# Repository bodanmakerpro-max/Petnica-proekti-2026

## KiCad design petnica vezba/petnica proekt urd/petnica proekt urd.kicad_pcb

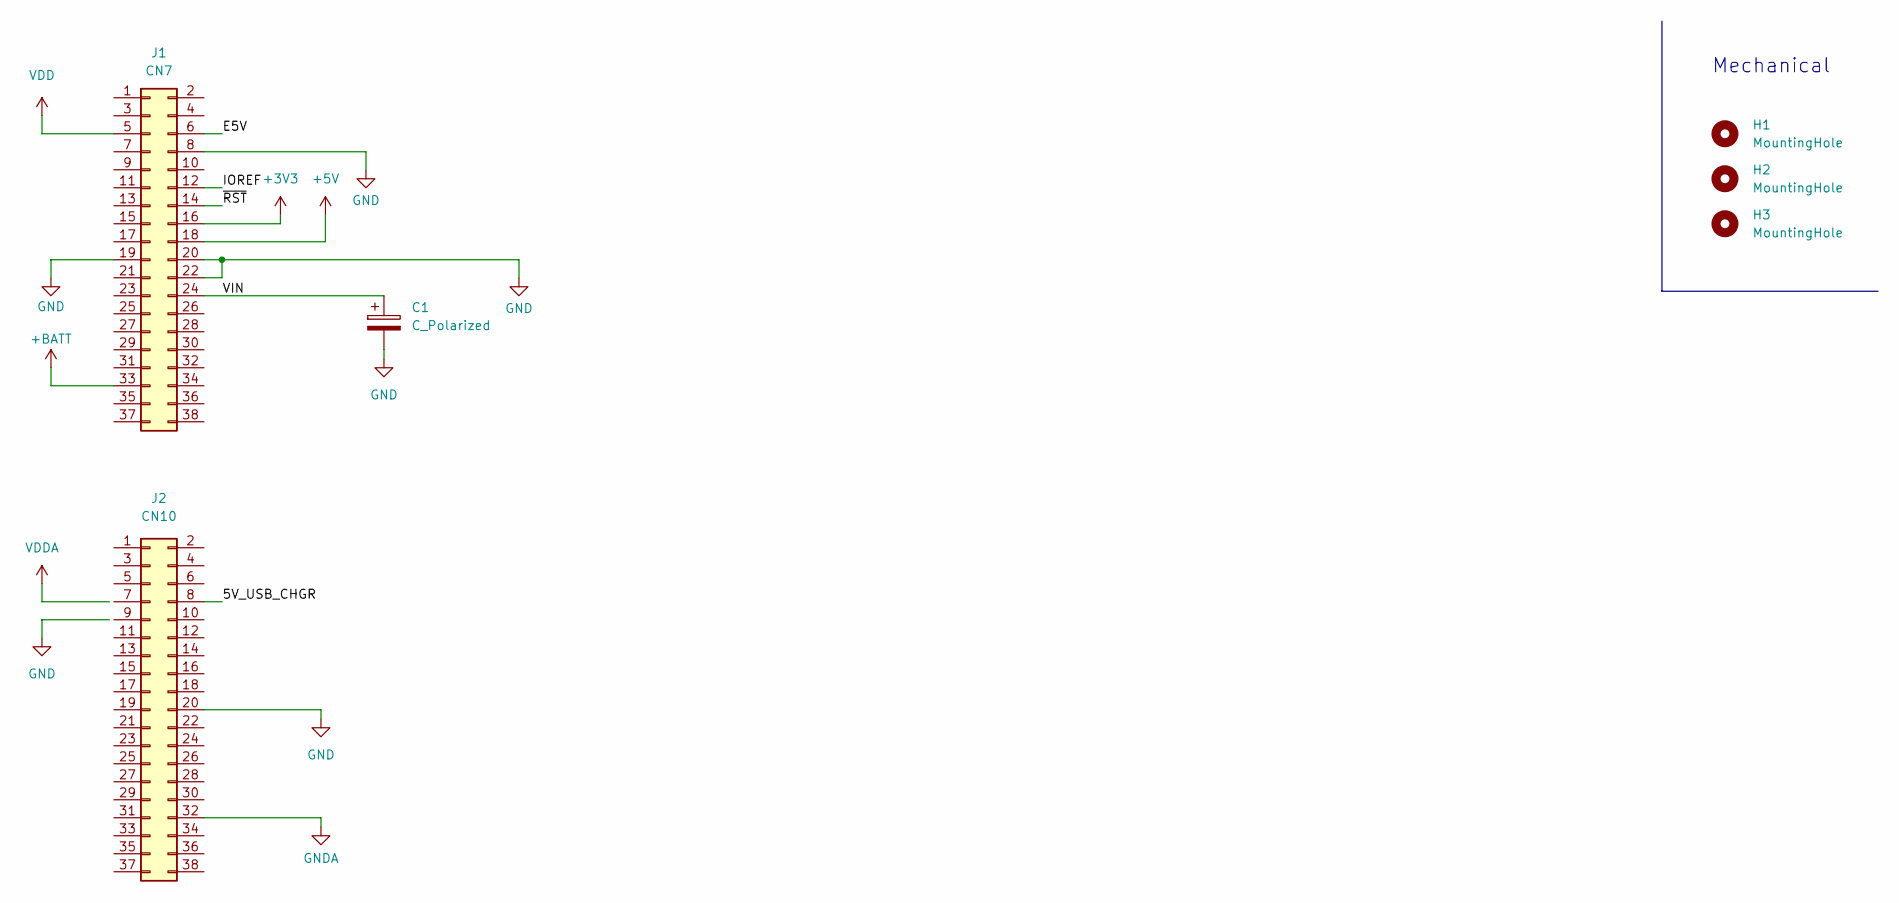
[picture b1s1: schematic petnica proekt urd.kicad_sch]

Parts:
C1: C_Polarized; CP_Radial_D13.0mm_P7.50mm
H1, H2, H3: MountingHole; MountingHole_3.2mm_M3
J1: CN7; PinSocket_2x19_P2.54mm_Vertical
J2: CN10; PinSocket_2x19_P2.54mm_Vertical

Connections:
+3V3: J1.16
+5V: J1.18
+BATT: J1.33
/5V_USB_CHGR: J2.8
/E5V: J1.6
/IOREF: J1.12
/VIN: C1.1, J1.24
/~RST: J1.14
GND: C1.2, J1.8, J1.19, J1.20, J1.22, J2.20
GNDA: J2.32
VDD: J1.5

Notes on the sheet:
Mechanical

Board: 2 copper layers, 6 parts (2 on the bottom side), 2 nets, no tracks yet.

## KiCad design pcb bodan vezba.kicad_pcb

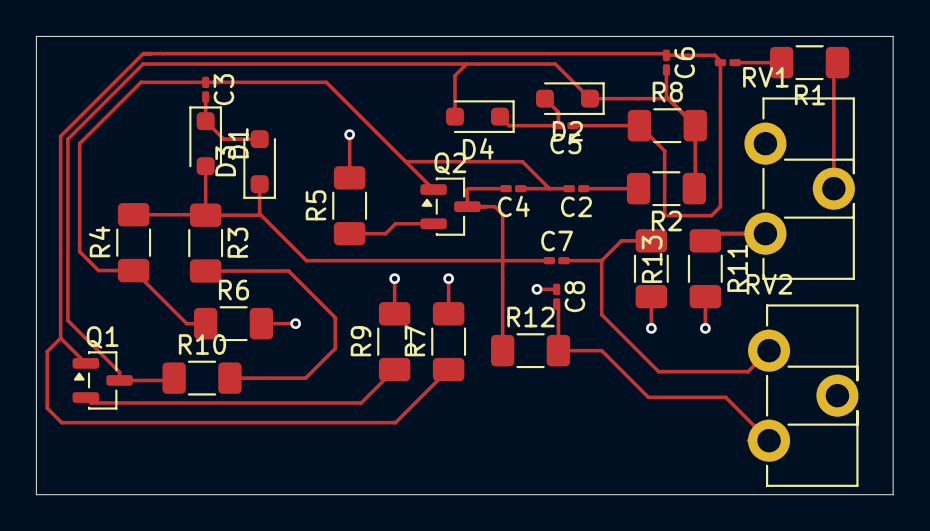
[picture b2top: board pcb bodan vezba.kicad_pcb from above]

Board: 2 copper layers, 47.6 x 25.5 mm, 29 parts (0 on the bottom side), 16 nets.

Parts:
C1, C2: 100n; C_0201_0603Metric_Pad0.64x0.40mm_HandSolder
C3, C5: 1u; C_0201_0603Metric_Pad0.64x0.40mm_HandSolder
C4, C6: 470p; C_0201_0603Metric_Pad0.64x0.40mm_HandSolder
C7: 4.7n; C_0201_0603Metric_Pad0.64x0.40mm_HandSolder
C8: 10n; C_0201_0603Metric_Pad0.64x0.40mm_HandSolder
D1, D2, D3, D4: 1N4148WS; D_SOD-323_HandSoldering
Q1, Q2: MMBT5551L; SOT-23
R1, R2, R3, R10: 10K; R_1206_3216Metric_Pad1.30x1.75mm_HandSolder
R4, R8: 470K; R_1206_3216Metric_Pad1.30x1.75mm_HandSolder
R5, R9: 150; R_1206_3216Metric_Pad1.30x1.75mm_HandSolder
R6, R7: 100K; R_1206_3216Metric_Pad1.30x1.75mm_HandSolder
R11: 1K; R_1206_3216Metric_Pad1.30x1.75mm_HandSolder
R12: 39K; R_1206_3216Metric_Pad1.30x1.75mm_HandSolder
R13: 22k; R_1206_3216Metric_Pad1.30x1.75mm_HandSolder
RV1, RV2: R_Potentiometer; Potentiometer_ACP_CA9-H3,8_Horizontal

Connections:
9V: R3.2, R10.2
GND: C8.1, R5.2, R6.2, R7.2, R9.2, R11.2, R13.2
unnamed: C1.1, R1.2
unnamed: C2.1, R2.2
unnamed: C7.2, R13.1, RV2.1
unnamed: C8.2, R12.2, RV2.3
unnamed: C4.2, C7.1, D1.2 (A), D3.1 (K), Q2.3 (C), R3.1, R4.2, R12.1
unnamed: C3.2, D1.1 (K), D3.2 (A)
unnamed: C5.2, D2.2 (A), D4.1 (K)
unnamed: C6.2, D2.1 (K), D4.2 (A), Q1.3 (C), R2.1, R8.2, R10.1
unnamed: C1.2, C5.1, C6.1, Q1.1 (B), R7.1, R8.1
unnamed: Q1.2 (E), R9.1
unnamed: C2.2, C3.1, C4.1, Q2.1 (B), R4.1, R6.1
unnamed: Q2.2 (E), R5.1
unnamed: R1.1, RV1.2
unnamed: R11.1, RV1.3

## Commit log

2026-04-17 vezba shematika
